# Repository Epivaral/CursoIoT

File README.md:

# Curso IoT
Material complementario del curso: INTRODUCCIÓN A IOT, ALMACENAMIENTO EN LA NUBE Y ANÁLISIS DE DATA

 Curso disponible aqui: <a href="https://www.youtube.com/playlist?list=PL22a5HPkoCQb2UCUi800SvnNu_HrKVk-G">Playlist Youtube</a> 
 
 ---
## Hardware

Modulos IoT para este curso, no necesitas todos, con un NodeMCU es mas que suficiente: 

- <a href="https://www.amazon.com/HiLetgo-Internet-Development-Wireless-Micropython/dp/B081CSJV2V">NodeMCU ESP8266</a>
- <a href="https://www.sparkfun.com/products/13711">SparkFun ESP8266 Thing - Dev Board</a>
- <a href="https://www.amazon.com/SongHe-Development-Dual-Mode-Bluetooth-Antenna/dp/B08246MCL5">ESP32</a>
- <a href="https://www.raspberrypi.org/products/raspberry-pi-4-model-b/">Raspberry Pi 3 o 4 (preferiblemente 4)</a>
- Distintos tipos de <a href="https://www.amazon.com/HiLetgo-Sensors-Assortment-Raspberry-Projects/dp/B01N5910XS">sensores</a> y <a href="https://www.amazon.com/Miuzei-Helicopter-Airplane-Remote-Control/dp/B07NSVKZP7">actuadores</a>

## Software

- <a href="https://azure.microsoft.com/en-us/free/">Cuenta de Azure</a>
- <a href="https://powerbi.microsoft.com/en-us/">PowerBI</a>
- <a href="https://www.arduino.cc/en/software">Arduino IDE</a>
- <a href="https://micropython.org/">MicroPython</a>
- <a href="https://thonny.org/">Thonny</a>
- <a href="https://code.visualstudio.com/">VSCode</a>
- <a href="https://visualstudio.microsoft.com/">Visual Studio</a>

 ---
 ## Modulo 1: Conceptos básicos
- <a href="https://www.youtube.com/watch?v=HuZQsPen9S4">Explicar qué es IoT y cómo puede ayudarnos.</a>
  - Conceptos básicos de hardware: explicar que es y cómo funciona el módulo que utilizamos
  - Conceptos básicos de los sensores y actuadores: cómo funciona un sensor y cómo podemos medirlos
  - Conceptos básicos del software: qué es un servicio en la nube y los servicios que utilizamos (base de datos, programación, análisis de datos, visualización de datos) y cómo podemos comunicarnos con un dispositivo.

## Módulo 2: Obtención de datos
Material complementario <a href="/Modulo 2/">Aqui ⬇</a>
- <a href="https://www.youtube.com/watch?v=DoEXbU-nT84">Configuración y programación básica de nuestro dispositivo ESP8266</a>
- Ejemplo simple sobre cómo conectar distintos sensores y actuadores:
  - <a href="https://www.youtube.com/watch?v=zQ4-adT0BSA">Encender y apagar LED</a>
  - <a href="https://www.youtube.com/watch?v=ASPIfFUboGs">Push Button</a>
  - <a href="https://www.youtube.com/watch?v=4Zcyb7DkYb8">Pulse Width Modulation</a>
  - <a href="https://www.youtube.com/watch?v=EF4Zmd-J-as">ADC</a>
  - <a href="https://www.youtube.com/watch?v=Pde4dbyZxSI">Sensor distancia (HC-SR04)</a>
  - <a href="https://www.youtube.com/watch?v=UKmICfz_fGk">Sensor humedad/temperatura (DHT22)</a>
  - <a href="https://www.youtube.com/watch?v=NvnP0YtsOvw">Motor DC (Driver TB6612FNG)</a>
  - <a href="https://www.youtube.com/watch?v=pxHsRv2epHE">Sensor efecto hall (Interrupts)</a>
  - <a href="https://www.youtube.com/watch?v=9Lu98LXeJOA">Servo</a>
  - <a href="https://www.youtube.com/watch?v=6NS6sh36p_A">Pantalla OLED (I2C)</a>

## Módulo 3: Habilitación de un dispositivo IoT para usar servicios en la nube
Material complementario <a href="/Modulo 3/">Aqui ⬇</a>
- <a href="https://www.youtube.com/watch?v=0CmfkGMnhA4">Introducción a MicroPython</a>
  - Configurar nuestro dispositivo para usar Micropython
- Configuración de nuestro dispositivo IoT para leer datos (librería WIFI)
  - <a href="https://www.youtube.com/watch?v=t-UXmWUz__4">Network Scan</a>
  - <a href="https://www.youtube.com/watch?v=sqay7rE_KRw">Modo Station</a>
  - <a href="https://www.youtube.com/watch?v=PGnoUtts3Ok">Modo Cliente</a>
  - <a href="https://www.youtube.com/watch?v=-z6-nZJdeBE">Modo Access Point</a>
  - <a href="https://www.youtube.com/watch?v=HjbEAuQXr1M">Web Server y utilización de Angular para interfaz de usuario enriquecida</a>
  - <a href="https://www.youtube.com/watch?v=RrHxOLSw3Jg">Desplegar lectura de sensores en web server</a>
  - <a href="https://www.youtube.com/watch?v=dEINx31FY00">Controlar un servo en WebServer</a>
- Comunicar nuestro dispositivo IoT a los servicios en la nube (Utilizando servicios de Azure)
  - <a href="https://www.youtube.com/watch?v=akre5_b_Eys">Conectarnos a Azure IoT Hub</a>
  - <a href="https://www.youtube.com/watch?v=BEc8bBKQDgU">Enviar telemetría a Azure IoT Hub</a>
  - <a href="https://www.youtube.com/watch?v=g5eH2h7WpdI">Recibir comandos desde Azure IoT Hub</a>

## Módulo 4: Análisis de datos
Material complementario <a href="/Modulo 4/">Aqui ⬇</a>
- <a href="https://www.youtube.com/watch?v=FtnQwAeIObw">Uso de procesos ETL para la limpieza y preparación de datos (servicios Azure)</a>
- <a href="https://www.youtube.com/watch?v=Wg2sIpVqDMo">Creación de un panel interactivo para visualizar los datos capturados (utilizando PowerBI)</a>

## Módulo 5: Retroalimentación del sistema
Material complementario <a href="/Modulo 5/">Aqui ⬇</a>
- <a href="https://www.youtube.com/watch?v=tObz4KHemeo">Configuración de un simple sistema sensor-actuador</a>
- <a href="https://www.youtube.com/watch?v=U1Ahw6HjE5s">Configuración de un sistema simple de registro y respuesta de datos</a>

## Modulo 6: Otras configuraciones
Material complementario <a href="/Modulo 6/">Aqui ⬇</a>
- <a href="https://www.youtube.com/watch?v=sraDWQduinE">Sleep</a>
- <a href="https://www.youtube.com/watch?v=1ezEOdePxiU">Persistir data</a>
- <a href="https://www.youtube.com/watch?v=_YsNYwx1vgc">OTA (over the air updates)</a>
- <a href="https://www.youtube.com/watch?v=xAELw8mDLFM">Otros boards mas potentes</a>
  - ESP32
  - Raspberry PI

## Módulo 7: Aplicacion real (* En progreso)
Material complementario <a href="/Modulo 7/">Aqui ⬇</a>
- Oxímetro digital capaz de medir el oxígeno en la sangre por medio del sensor max30102 y un ESP 32.
  - Lista de posibles funcionalidades:
    - Diseño para ser portátil, optimizar el uso de batería siempre que sea posible
    - Opción a conexión wifi, si no se tiene una red cerca, guardar mediciones en la memoria FLASH
    - Control web con sistema de alarma en caso de que no se haya hecho medición en N horas

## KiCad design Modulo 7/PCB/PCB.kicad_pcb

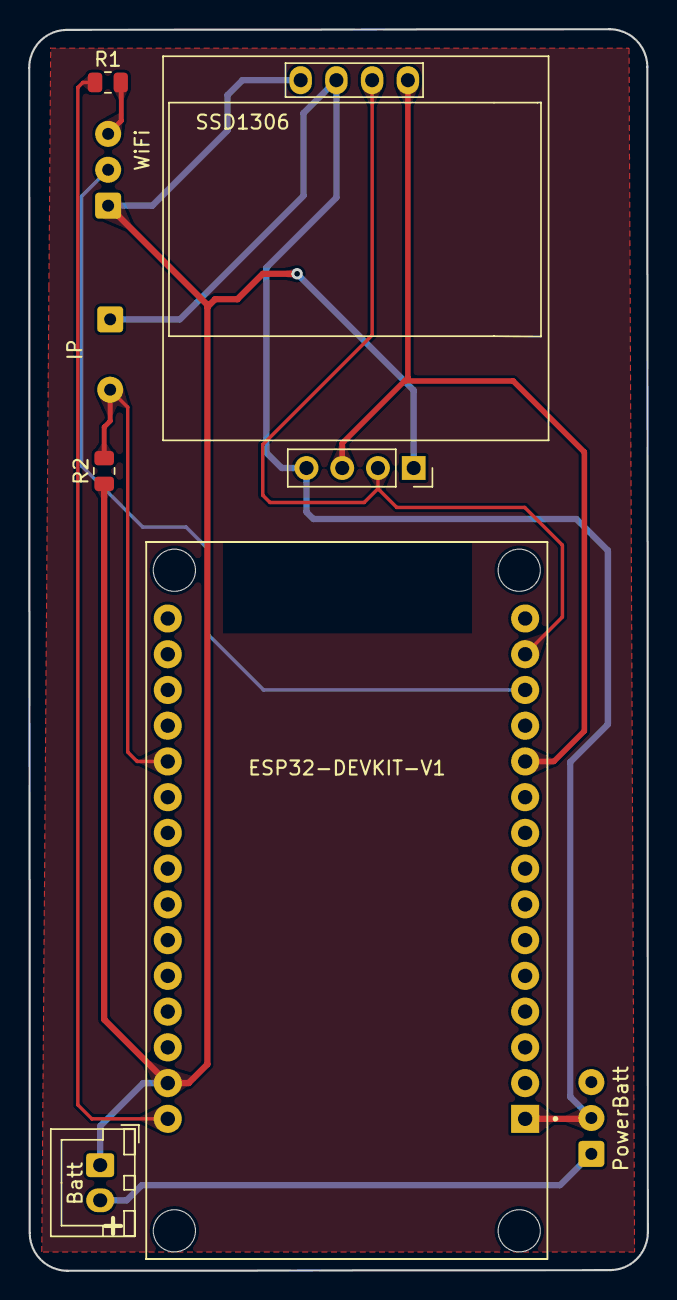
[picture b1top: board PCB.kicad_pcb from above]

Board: 2 copper layers, 44.0 x 88.2 mm, 9 parts (0 on the bottom side), 9 nets.

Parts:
Brd1: SSD1306; 128x64OLED
J1: Batt; JST_XH_B2B-XH-A_1x02_P2.50mm_Vertical
R1, R2: 10K; R_0805_2012Metric
SW1: PowerBatt; SolderWire-0.25sqmm_1x03_P4.2mm_D0.65mm_OD1.7mm
SW2: WiFi; SolderWire-0.25sqmm_1x03_P4.2mm_D0.65mm_OD1.7mm
SW3: IP; SolderWire-0.25sqmm_1x02_P4.2mm_D0.65mm_OD1.7mm
U1: ESP32-DEVKIT-V1; MODULE_ESP32_DEVKIT_V1
U2: MAX30102; PinSocket_1x04_P2.54mm_Vertical

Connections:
/+: J1.2, SW1.1 (A)
/GND: Brd1.1 (GND), J1.1, R2.1, SW2.1 (A), U1.2 (GND), U1.29 (GND), U2.1 (NC)
/Vdd: Brd1.2 (VCC), SW1.2 (B), SW3.1, U1.1 (3V3)
unnamed: Brd1.3 (SCL), U1.14 (D22), U2.2 (SCL)
unnamed: Brd1.4 (SDA), U1.11 (D21), U2.3 (SDA)
unnamed: SW2.2 (B), U1.13 (TX0)
unnamed: R1.2, SW2.3 (C)
unnamed: R2.2, SW3.2, U1.20 (D35)
unnamed: R1.1, U1.30 (VIN)

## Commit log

2020-12-12 Video 5
2020-12-12 folder name change
2020-12-19 New demos
2021-01-23 11 y 12
2021-03-06 Demo 2
2021-03-13 Mod3
2021-03-18 vid 6 y 7
2021-03-22 Vid 7
2021-04-29 Video 10
2021-05-13 Video 11
2021-06-06 Modulo 4
2021-06-24 Modulo 5 01
2021-09-04 Modulo 5 y 6
2021-10-24 video 3 y 4
2023-03-10 Medicion de SPO2 y Pulso usando sensor MAX30102
2023-03-12 Diseño PCB
2023-04-08 Battery saving improvements
